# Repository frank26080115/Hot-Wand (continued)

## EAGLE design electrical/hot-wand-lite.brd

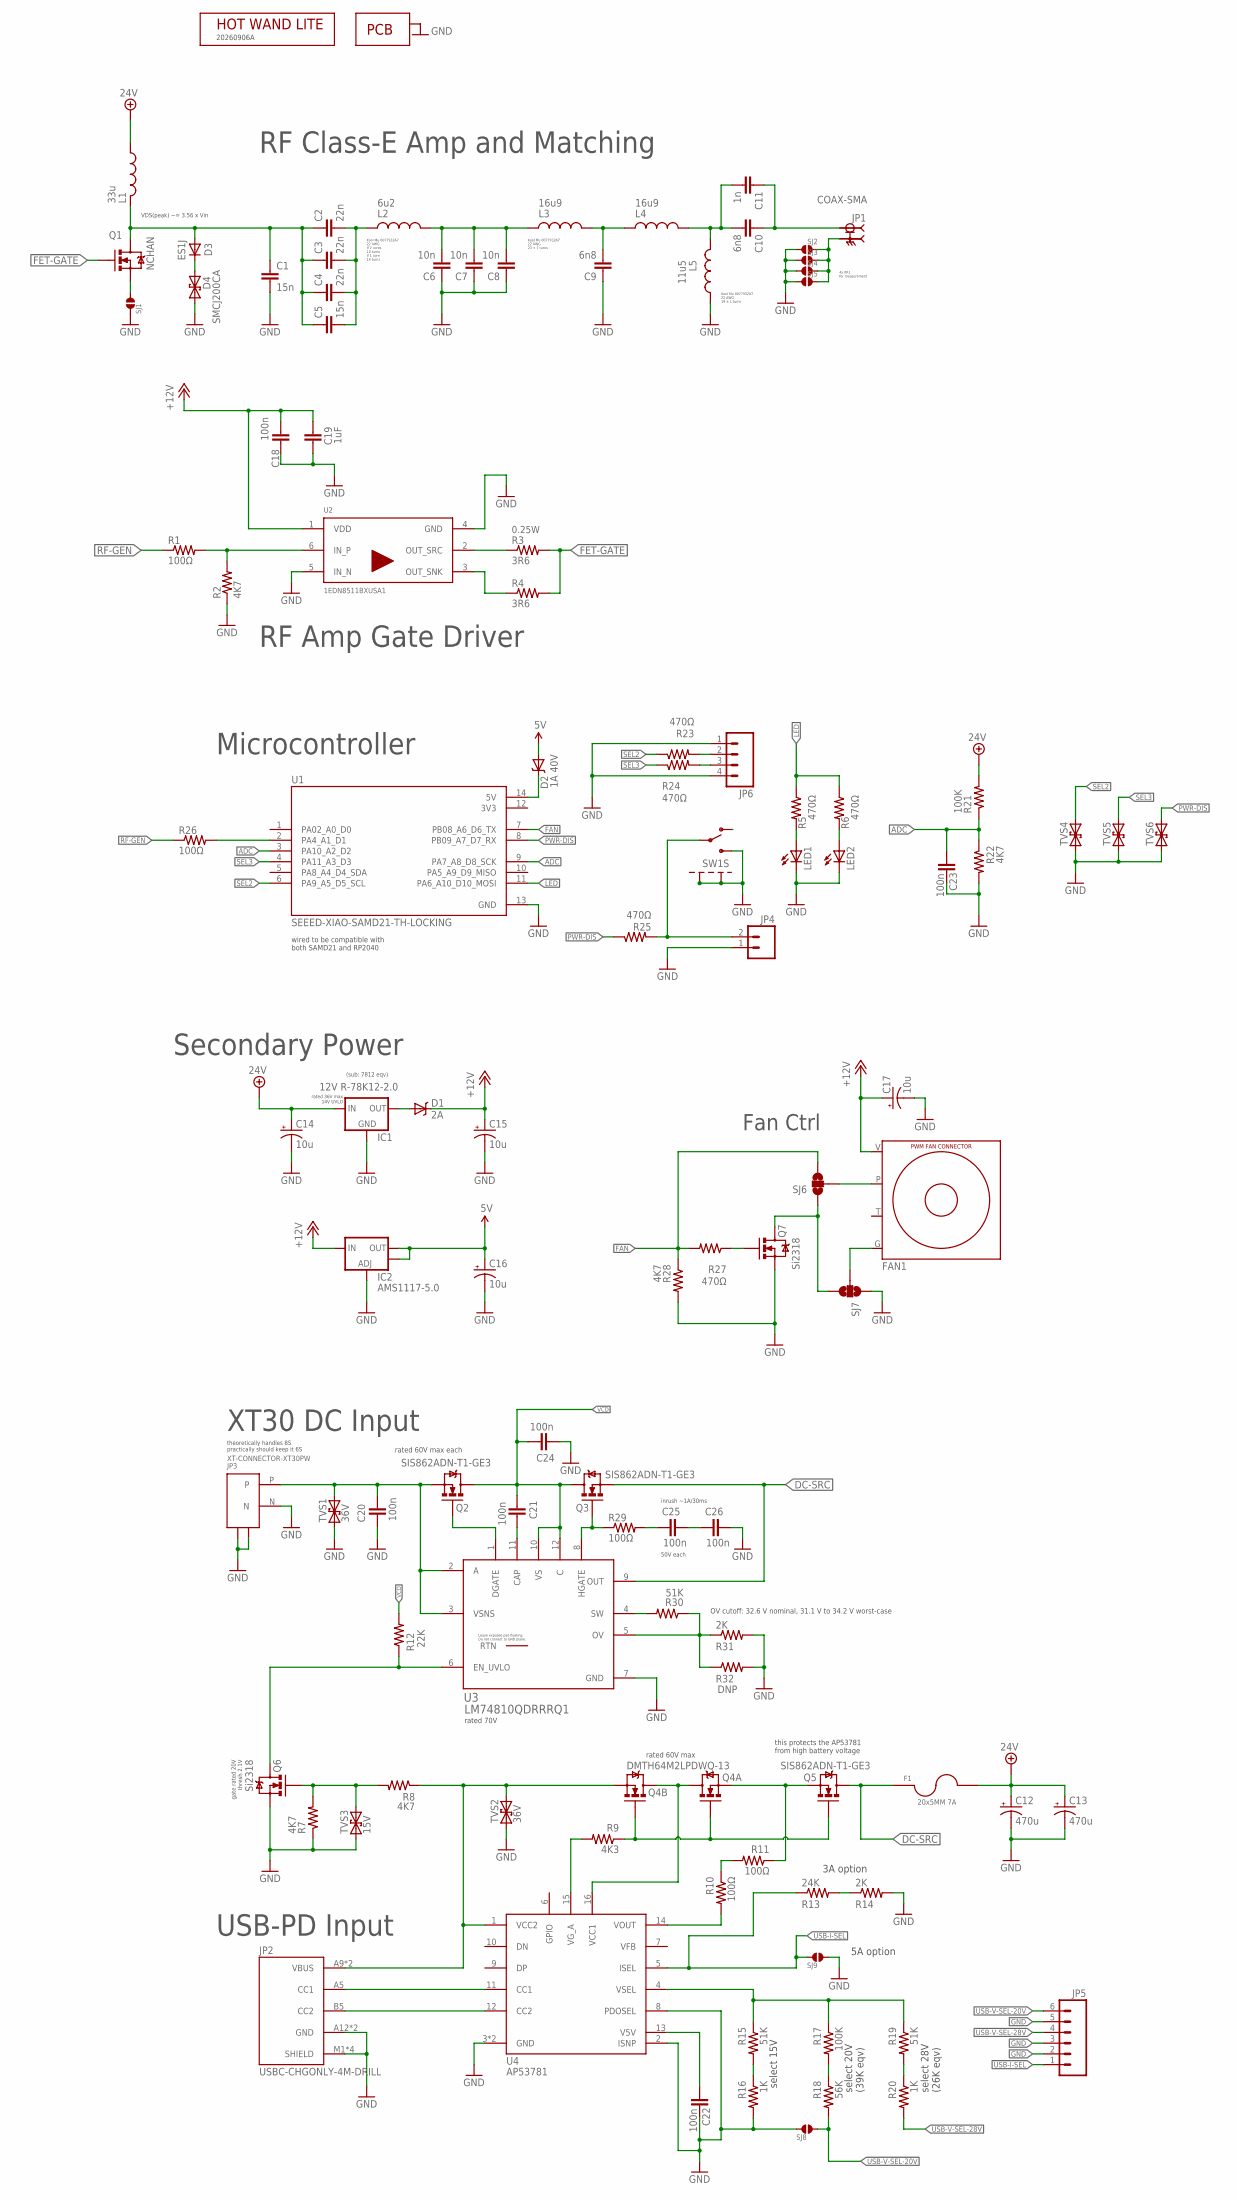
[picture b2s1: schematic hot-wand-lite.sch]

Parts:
C1, C5: 15n; 1206; PARTNUM C3216C0G2E153J160AA; JLCPARTNUM C3858208
C2, C3: 22n; 1206; JLCPARTNUM C3862155
C4: 22n; 1206; PARTNUM GCM31C5C2E223JX03L; JLCPARTNUM C3862155
C6: 10n; 1206; PARTNUM C3216C0G2E103J115AA; JLCPARTNUM C2261646;C2170837;C2175075
C7, C8: 10n; 1206; PARTNUM GRM31B5C2E103JWA1L; JLCPARTNUM C2261646
C9, C10: 6n8; 1206; PARTNUM C1206C682JCGACAUTO; JLCPARTNUM C2182121
C11: 1n; 1206; PARTNUM GCM31C5C3A102FX03L; JLCPARTNUM C3859218
C12, C13: 470u; CPOL-RADIAL-COMBO-10MM; PARTNUM UHW1H471MPD; JLC-DNP 1
C14, C17: 10u; EIA3216-KIT; PARTNUM MLASU31LBB5106KTNA01;GRT31CR61H106KE01K; JLCPARTNUM C13585
C15, C16: 10u; EIA3216-KIT; PARTNUM TAJA106K016TNJ;T491A106K016AT; JLCPARTNUM C13585
C18, C20, C21, C22, C23, C24, C25, C26: 100n; 0603-CAP; JLCPARTNUM C14663
C19: 1uF; 0603-CAP; JLCPARTNUM C15849
D1: 2A; SMA-DIODE; PARTNUM VSSAF5N50;SL36A; JLCPARTNUM C698873
D2: 1A 40V; SOD123FL; JLCPARTNUM C8598
D3: ES1J; SMA-DIODE; JLCPARTNUM C64879
D4: SMCJ200CA; SMC; JLCPARTNUM C2760132
F1: 20x5MM 7A; FUSE_5MM; PARTNUM 3518P; JLC-DNP 1
FAN1: FAN-CONN-X4-CONN-X4; FAN-CONN-X4; PARTNUM 0470531000
IC1: 12V R-78K12-2.0; TO220-BUCK-12V; PARTNUM R-78K12-2.0; JLC-DNP 1
IC2: AMS1117-5.0; SOT223; PARTNUM AMS1117-5.0; JLCPARTNUM C6187
JP1: COAX-SMA; SAMTEC_SMA-J-P-H-ST-EM1-LGRPAD; PARTNUM SMA-J-P-H-ST-EM1; JLC-DNP 1
JP2: USBC-CHGONLY-4M-DRILL; SAMESKY_UJC-H-G-SMT-2-P6-TR-DRILL; PARTNUM UJC-H-G-SMT-P6-TR; JLC-DNP 1
JP3: XT-CONNECTOR-XT30PW; XT30PW; PARTNUM XT30PW-M; JLC-DNP 1
JP4: M02PTH3; 1X02_LONGPADS; JLC-DNP 1
JP5: M06LOCK; 1X06_LOCK
JP6: M04LOCK; 1X04_LOCK; JLC-DNP 1
L1: 33u; IND_SRP1265A; PARTNUM PA4343.333NLT;SRP1265A-330M;SRP1265CC-3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; JLCPARTNUM C2453886
L2: 6u2; IND-KOOLMU-2W; JLC-DNP 1
L3, L4: 16u9; IND-KOOLMU; JLC-DNP 1
L5: 11u5; IND-KOOLMU; JLC-DNP 1
LED1: LED; LED_LTST-S220KRKT; PARTNUM LTST-S220KRKT; JLCPARTNUM C284935
LED2: LED; LED-0603; JLC-DNP 1
PCB1: PCB-OUTLINE; JLC-DNP 1
PCB2: PCB-ART-VER-LITE; PCB-ART-VERSION-LITE; JLC-DNP 1
Q1: NCHAN; TO247-COMBO; JLC-DNP 1
Q2, Q3, Q5: SIS862ADN-T1-GE3; POWERPAK-1212-8; PARTNUM SIS862ADN-T1-GE3; JLC-DNP 1
Q4: DMTH64M2LPDWQ-13; POWERPAK-SO8-X2; PARTNUM DMTH64M2LPDWQ-13; JLC-DNP 1
Q6: Si2318; SOT23-3; PARTNUM 2N7002K;SSM3K388R,LF;Si2318CDS-T1-GE3;P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; JLCPARTNUM C14498;C547263;C5224211;C54347659
Q7: Si2318; SOT23-3; PARTNUM G3404;MMFTN3404A;PJA3404A;Si2318CDS-T1-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; JLCPARTNUM C14498;C547263;C96615
R1, R10, R11, R26, R29: 100Ω; 0805; JLCPARTNUM C441975
R2, R7, R8, R22, R28: 4K7; 0603-RES; JLCPARTNUM C23162
R3, R4: 3R6; 0603-RES; JLCPARTNUM C445783
R5, R6, R23, R24, R25, R27: 470Ω; 0603-RES; JLCPARTNUM C23179
R9: 4K3; 0603-RES; JLCPARTNUM C23159
R12: 22K; 0603-RES; JLCPARTNUM C31850
R13: 24K; 0603-RES; JLCPARTNUM C23352
R14, R31: 2K; 0603-RES; JLCPARTNUM C22975
R15, R19, R30: 51K; 0603-RES; JLCPARTNUM C23196
R16, R20: 1K; 0603-RES; JLCPARTNUM C21190
R17, R21: 100K; 0603-RES; JLCPARTNUM C25803
R18: 56K; 0603-RES; JLCPARTNUM C23206
R32: DNP; 0603-RES
SJ1, SJ2, SJ3, SJ4, SJ5: SJ-SMALL-1206-SJ; 1206-SJ
SJ6, SJ7: SOLDERJUMPER_2WAYS; SJ_3
SJ8, SJ9: SJ-SMALL-2S-NO; SJ_2S-NO
SW1: SWITCH-SPDT-2MNT-SLW-864574-5A-RA-N-D; SWITCH-SLW-864574-5A-RA-N-D; PARTNUM SLW-864574-5A-RA-N-D; JLC-DNP 1
TVS1, TVS2: 36V; SMA; PARTNUM SMAJ36CA; JLCPARTNUM C134984
TVS3: 15V; SOD-323; PARTNUM SD15C-01FTG;CDSOD323-T15SC;TSD15CDYFR; JLCPARTNUM C2987151
TVS4, TVS5, TVS6: TVSSOD323-R; SOD323-R; JLCPARTNUM C840638
U1: SEEED-XIAO-SAMD21-TH-LOCKING; MODULE_102010388_LOCKING; JLC-DNP 1
U2: 1EDN8511BXUSA1; SOT95P280X145-6N-7-V; JLCPARTNUM C3655509
U3: LM74810QDRRRQ1; DRR0012E-MFG; JLCPARTNUM C3215601
U4: AP53781; QFN3030-16; JLCPARTNUM C52730979

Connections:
3V3: U1.12 (3V3)
5V: C16.A (+), D2.A, IC2.2 (OUT), IC2.4 (OUT)
12V-2: D1.A, IC1.3 (OUT)
+12V: C15.A (+), C17.A (+), C18.2, C19.2, D1.C, FAN1.V, IC2.3 (IN), U2.1 (VDD)
+24V: C12.1 (+), C12.1B (+), C13.1 (+), C13.1B (+), C14.A (+), F1.3 (2), F1.4 (2), IC1.1 (IN), L1.1, R21.2
ADC: C23.2, R21.1, R22.1, U1.3 (PA10_A2_D2), U1.9 (PA7_A8_D8_SCK)
DC-SRC: F1.1, F1.2 (1), Q3.1 (S), Q3.2 (S), Q3.3 (S), Q5.5 (D), Q5.6 (D), Q5.7 (D), Q5.8 (D), Q5.9 (D), U3.9 (OUT)
FAN: R27.2, R28.1, SJ6.3, U1.7 (PB08_A6_D6_TX)
FET-GATE: Q1.1 (G), Q1.1B (G), R3.2, R4.2
GND: C1.2, C6.1, C7.1, C8.1, C9.1, C12.2 (-), C12.2B (-), C13.2 (-), C13.2B (-), C14.C (-), C15.C (-), C16.C (-), C17.C (-), C18.1, C19.1, C20.2, C22.1, C23.1, C24.2, C26.1, D4.A (1), IC1.2 (GND), IC2.1 (ADJ), JP2.A12 (GND), JP2.B12 (GND), JP2.M1 (SHIELD), JP2.M2 (SHIELD), JP2.M3 (SHIELD), JP2.M4 (SHIELD), JP3.M1, JP3.M2, JP3.N, JP4.1, JP5.2, JP5.3, JP5.5, JP6.1, JP6.4, L5.1, LED1.C, LED2.C, PCB1.1, PCB1.2, PCB1.3, PCB1.4, Q6.2 (S), Q7.2 (S), R2.1, R7.1, R14.2, R16.2, R22.2, R28.2, R31.2, R32.2, SJ1.1, SJ2.2, SJ3.2, SJ4.2, SJ5.2, SJ7.1, SJ8.1, SJ9.2, SW1.M1 (MNT1), SW1.M2 (MNT2), SW1.R (S), TVS1.A (1), TVS2.A (1), TVS3.2 (1), TVS4.A (1), TVS5.A (1), TVS6.A (1), U1.13 (GND), U2.4 (GND), U2.5 (IN_N), U3.7 (GND), U4.2 (ISNP), U4.3 (GND), U4.8 (PDOSEL), U4.EXP (GND)
LED: R5.1, R6.1, U1.11 (PA6_A10_D10_MOSI)
M1: C2.2, C3.2, C4.2, C5.2, L2.1A (1), L2.1B (1), L2.1C (1), L2.1D (1)
M2: C6.2, C7.2, C8.2, L2.2A (2), L2.2B (2), L2.2C (2), L2.2D (2), L3.1
M3: C9.2, L3.2, L4.1
M4: C10.2, C11.2, L4.2, L5.2
MCU-RF: R1.2, R2.2, U2.6 (IN_P)
MOSFET-DRAIN: C1.1, C2.1, C3.1, C4.1, C5.1, D3.A, L1.2, Q1.2 (D)
MOSFET-SOURCE: Q1.3 (S), Q1.3B (S), SJ1.2
unnamed: R17.2, R18.1
unnamed: LED2.A, R6.2
unnamed: R15.2, R16.1
unnamed: R13.2, R14.1
unnamed: R19.2, R20.1
unnamed: R3.1, U2.2 (OUT_SRC)
unnamed: R4.1, U2.3 (OUT_SNK)
unnamed: Q4.1 (S), Q5.1 (S), Q5.2 (S), Q5.3 (S), R11.1
unnamed: JP6.2, R23.2
unnamed: JP6.3, R24.2
unnamed: Q7.1 (G), R27.1
unnamed: FAN1.P, SJ6.2
unnamed: JP4.2, R25.2, SW1.C
unnamed: Q7.3 (D), SJ6.1, SJ7.3
unnamed: D2.C, U1.14 (5V)
unnamed: FAN1.G, SJ7.2
unnamed: D3.C, D4.C (2)
unnamed: C25.1, C26.2
unnamed: Q6.1 (G), R7.2, R8.2, TVS3.1 (2)
unnamed: Q4.5 (D), Q4.6 (D), Q4.7 (D), Q4.8 (D), Q4.9 (D), Q4.10 (D), U4.16 (VCC1)
unnamed: C22.2, U4.13 (V5V)
unnamed: R10.2, U4.14 (VOUT)
unnamed: C25.2, R29.2
unnamed: LED1.A, R5.2
unnamed: R10.1, R11.2
unnamed: R30.2, U3.4 (SW)
unnamed: C21.1, U3.11 (CAP)
PWR-DIS: R25.1, TVS6.C (2), U1.8 (PB09_A7_D7_RX)
RF-GEN: R1.1, R26.1
RF-GEN-PRE: R26.2, U1.2 (PA4_A1_D1)
RF-OUT: C10.1, C11.1, JP1.1
RF-RETURN: JP1.2_1 (2), JP1.2_2 (2), JP1.3_1 (2), JP1.3_2 (2), SJ2.1, SJ3.1, SJ4.1, SJ5.1
SEL2: R23.1, TVS4.C (2), U1.6 (PA9_A5_D5_SCL)
SEL3: R24.1, TVS5.C (2), U1.4 (PA11_A3_D3)
U3-DGATE: Q2.4 (G), U3.1 (DGATE)
U3-EN: Q6.3 (D), R12.1, U3.6 (EN_UVLO)
U3-HGATE: Q3.4 (G), R29.1, U3.8 (HGATE)
U3-OV: R30.1, R31.1, R32.1, U3.5 (OV)
U4-VGA: R9.2, U4.15 (VG_A)
U4-VGA-2: Q4.2 (G), Q4.4 (G), Q5.4 (G), R9.1
U4-VSEL: R15.1, R17.1, R19.1, U4.4 (VSEL)
USB-CC1: JP2.A5 (CC1), U4.11 (CC1)
USB-CC2: JP2.B5 (CC2), U4.12 (CC2)
USB-I-SEL: JP5.1, R13.1, SJ9.1, U4.5 (ISEL)
USB-V-SEL-20V: JP5.6, R18.2, SJ8.2
USB-V-SEL-28V: JP5.4, R20.2
USB-VBUS: JP2.A9 (VBUS), JP2.B9 (VBUS), Q4.3 (S), R8.1, TVS2.C (2), U4.1 (VCC2)
VCD: C21.2, C24.1, Q2.5 (D), Q2.6 (D), Q2.7 (D), Q2.8 (D), Q2.9 (D), Q3.5 (D), Q3.6 (D), Q3.7 (D), Q3.8 (D), Q3.9 (D), R12.2, U3.10 (VS), U3.12 (C)
VIN-XT30: C20.1, JP3.P, Q2.1 (S), Q2.2 (S), Q2.3 (S), TVS1.C (2), U3.2 (A), U3.3 (VSNS)

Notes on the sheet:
RF Amp Gate Driver
Secondary Power
select 15V
USB-PD Input
gate rated 20V thresh 2.1V
Microcontroller
rated 36V max 14V UVLO
select 20V (39K eqv)
RF Class-E Amp and Matching
wired to be compatible with both SAMD21 and RP2040
(sub: 7812 eqv)
Kool Mu 0077932A7 22 AWG if 2 cores 10 turns if 1 core 14 turns
Kool Mu 0077932A7 22 AWG 23 ± 1 turns
Kool Mu 0077932A7 22 AWG 19 ± 1 turns
3A option
5A option
4x 0R1 for measurement
select 28V (26K eqv)
0.25W
theoretically handles 8S practically should keep it 6S
XT30 DC Input
rated 60V max each
rated 70V
rated 60V max
50V each
inrush ~1A/30ms
OV cutoff: 32.6 V nominal, 31.1 V to 34.2 V worst-case
this protects the AP53781 from high battery voltage
VDS(peak) ~= 3.56 x Vin
Fan Ctrl

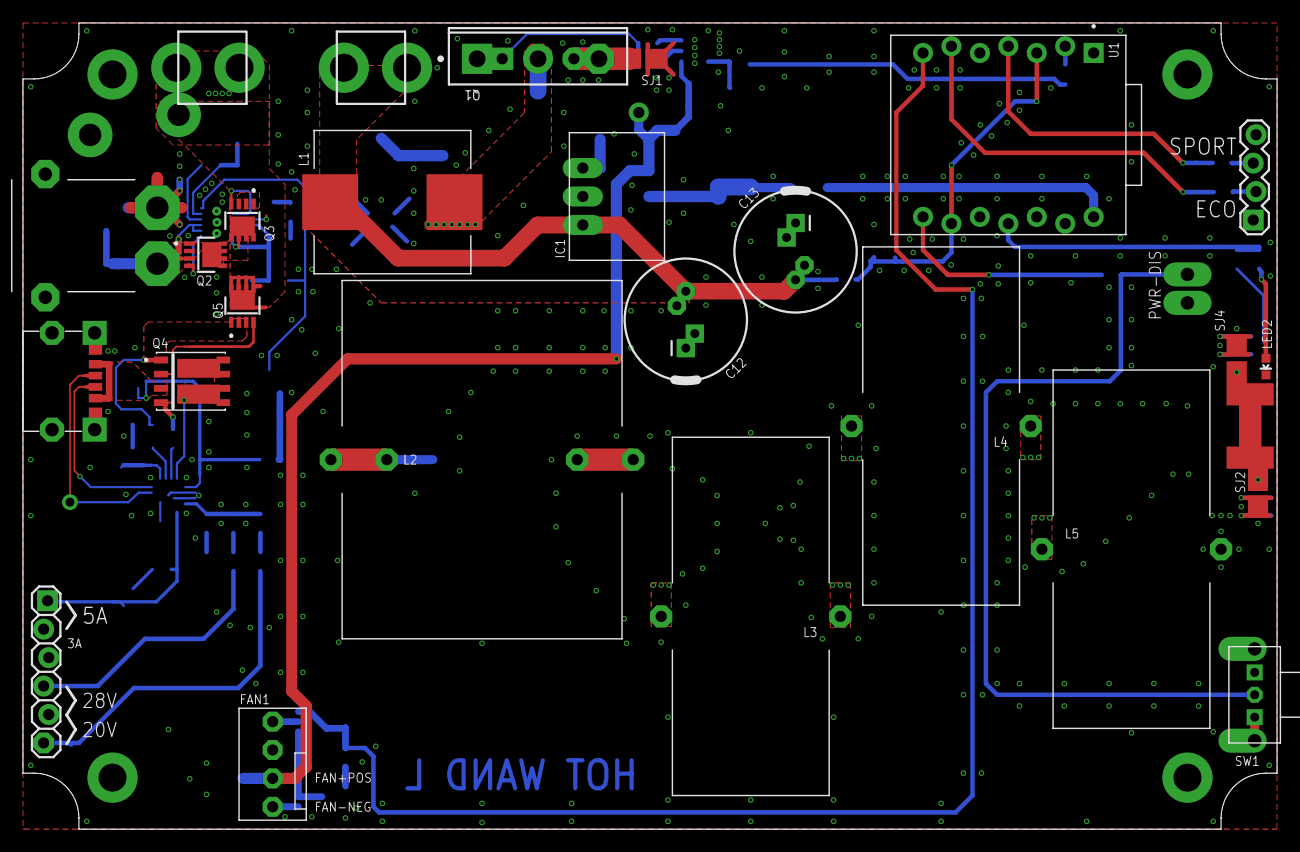
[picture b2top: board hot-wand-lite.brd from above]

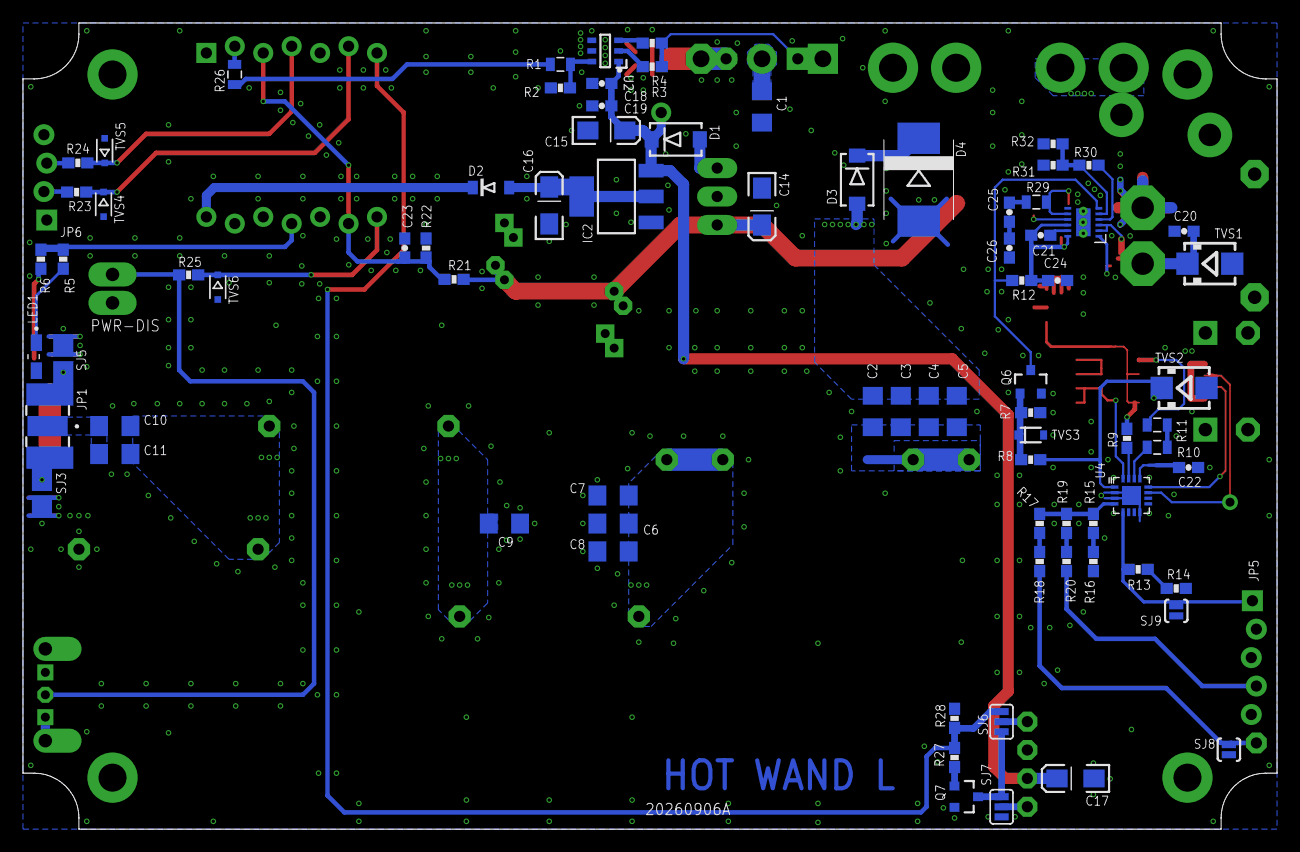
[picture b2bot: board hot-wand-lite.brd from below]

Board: 2 copper layers, 112.0 x 72.0 mm, 108 parts (81 on the bottom side), 66 nets.

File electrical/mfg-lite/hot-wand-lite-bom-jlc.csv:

Comment,Designator,Footprint,LCSC Part #
,JP5,1X06_LOCK,
,TVS4,SOD323-R,C840638
,TVS5,SOD323-R,C840638
,TVS6,SOD323-R,C840638
1A 40V,D2,SOD123FL,C8598
1EDN8511BXUSA1,U2,SOT95P280X145-6N-7-V,C3655509
1K,R16,0603-RES,C21190
1n,C11,1206,C3859218
1uF,C19,0603-CAP,C15849
2A,D1,SMA-DIODE,C698873
2K,R14 R31,0603-RES,C22975
3R6,R3 R4,0603-RES,C445783
4K3,R9,0603-RES,C23159
4K7,R2 R7 R8 R22 R28,0603-RES,C23162
6n8,C9 C10,1206,C2182121
10n,C6 C7 C8,1206,C2261646
10u,C14 C15 C16 C17,EIA3216-KIT,C13585
15V,TVS3,SOD-323,C2987151
15n,C1 C5,1206,C3858208
22K,R12,0603-RES,C31850
22n,C2 C3 C4,1206,C3862155
24K,R13,0603-RES,C23352
33u,L1,IND_SRP1265A,C2453886
36V,TVS1 TVS2,SMA,C134984
51K,R15 R30,0603-RES,C23196
56K,R18,0603-RES,C23206
100K,R17 R21,0603-RES,C25803
100n,C18 C20 C21 C22 C23 C24 C25 C26,0603-CAP,C14663
100,R1 R10 R11 R26 R29,0805,C441975
470,R5 R6 R23 R24 R25 R27,0603-RES,C23179
AMS1117-5.0,IC2,SOT223,C6187
AP53781,U4,QFN3030-16,C52730979
ES1J,D3,SMA-DIODE,C64879
FAN-CONN-X4-CONN-X4,FAN1,FAN-CONN-X4,
LED,LED1,LED_LTST-S220KRKT,C284935
LM74810QDRRRQ1,U3,DRR0012E-MFG,C3215601
SMCJ200CA,D4,SMC,C2760132
Si2318,Q6 Q7,SOT23-3,C14498;C547263;C96615

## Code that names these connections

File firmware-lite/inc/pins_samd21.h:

#pragma once

// Board-level pin assignments traced from electrical/hot-wand-lite.sch.

#if HOT_WAND_TARGET_XIAO_SAMD21 == 1

// XIAO D1/A1 is SAMD21 PA04 and provides TCC0/WO[0].
#define RFGEN_PIN D1

// The schematic's active-high LED net is XIAO D10/A10, SAMD21 PA06.
#define BLINK_LED_PIN D10

// XIAO's active-low onboard user LED is Arduino pin 13, SAMD21 PA17.
#define BLINK_XIAOBUILTIN_LED_PIN LED_BUILTIN

// Power-selection jumpers: names match their JP6 connector pin numbers.
#define SEL2_PIN D5 // XIAO D5/A5, SAMD21 PA09.
#define SEL3_PIN D4 // XIAO D4/A4, SAMD21 PA08.

// Active-low power switch: XIAO D9/A9, SAMD21 PA05.
#define POWER_SWITCH_PIN D9

// Active-high fan control: XIAO D7/A7, SAMD21 PB09.
#define FAN_CONTROL_PIN D7

// Both footprint pads are connected to the voltage-sense net. This target uses
// XIAO D8/A8 (SAMD21 PA07) for ADC and must leave D2 high-impedance.
#define ADC_PIN D8
#define ADC_UNUSED_PIN D2

#endif
